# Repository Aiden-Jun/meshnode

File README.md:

# meshnode

A screenless Meshtastic node built around a Seeed Studio XIAO nRF52840 and a Wio-SX1262 LoRa module.

## Hardware

- **U1** — Seeed Studio XIAO nRF52840 (MCU + BLE, handles charging and USB)
- **U2** — Wio-SX1262 LoRa module
- **J1** — 2-pin JST 1.25mm connector for a single-cell LiPo battery
- **SW2** — slide switch, gates power to the LoRa radio only (see below)
- **J5 / J6** — solder pads for a hand-wired bodge to the XIAO's battery pads (see below)

## Repo contents

- `meshnode.kicad_pro` / `.kicad_sch` / `.kicad_pcb` — KiCad 8 project
- `meshnode.step` / `.wrl` — 3D board exports
- `Gerber/` — fabrication outputs (Gerbers + drill files)

## Building

Open `meshnode.kicad_pro` in KiCad. Run ERC and DRC before sending to fab

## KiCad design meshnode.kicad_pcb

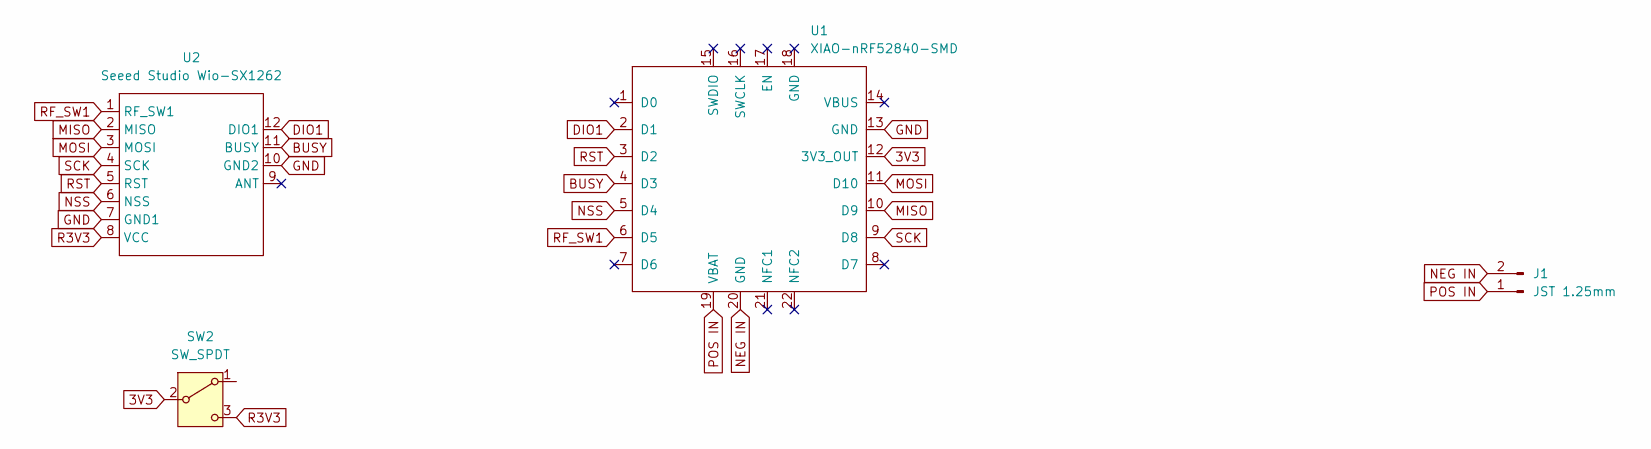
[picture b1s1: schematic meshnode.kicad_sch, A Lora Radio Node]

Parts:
J1: JST 1.25mm; Molex_PicoBlade_53048-0210_1x02_P1.25mm_Horizontal
SW2: SW_SPDT; SW_Slide_SPDT_Angled_CK_OS102011MA1Q
U1: XIAO-nRF52840-SMD
U2: Seeed Studio Wio-SX1262; Wio-SX1262 PCB Package

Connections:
3V3: SW2.2 (B), U1.12 (3V3_OUT)
BUSY: U1.4 (D3), U2.11 (BUSY)
DIO1: U1.2 (D1), U2.12 (DIO1)
GND: U1.13 (GND), U2.7 (GND1), U2.10 (GND2)
MISO: U1.10 (D9), U2.2 (MISO)
MOSI: U1.11 (D10), U2.3 (MOSI)
NEG IN: J1.2, U1.20 (GND)
NSS: U1.5 (D4), U2.6 (NSS)
POS IN: J1.1, U1.19 (VBAT)
R3V3: SW2.3 (C), U2.8 (VCC)
RF_SW1: U1.6 (D5), U2.1 (RF_SW1)
RST: U1.3 (D2), U2.5 (RST)
SCK: U1.9 (D8), U2.4 (SCK)

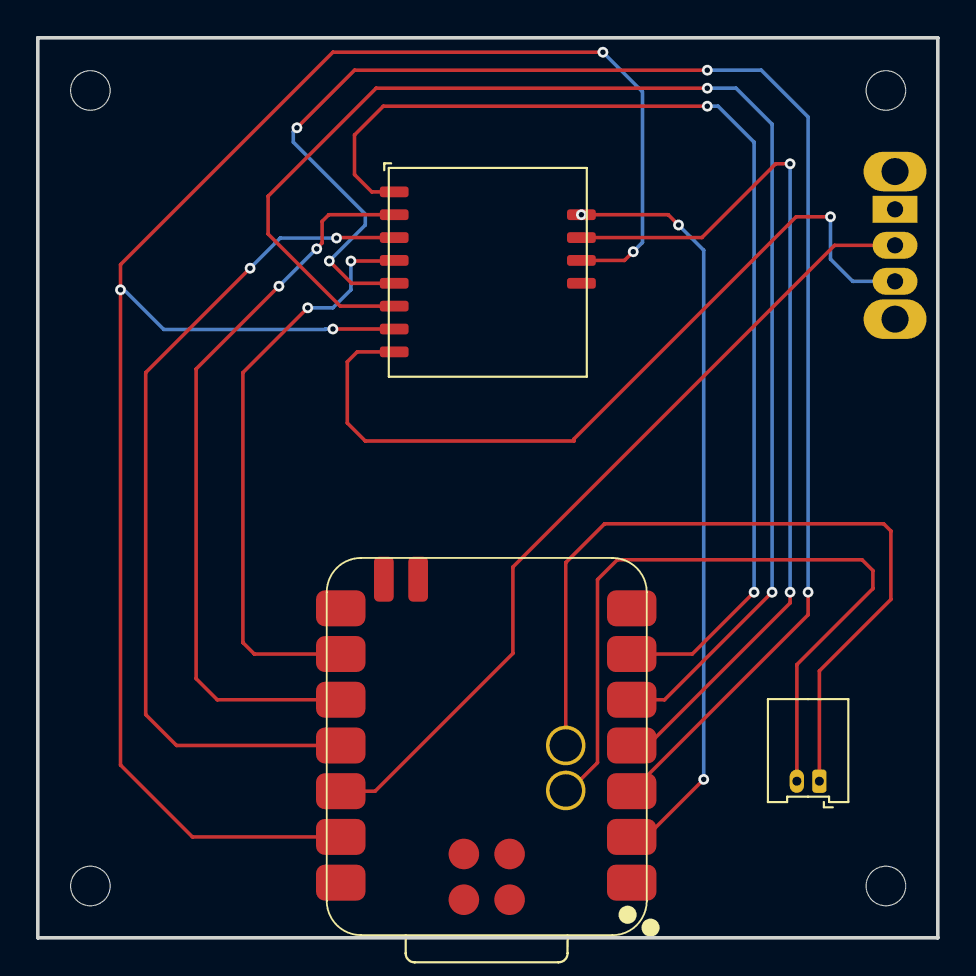
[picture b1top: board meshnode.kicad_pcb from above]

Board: 2 copper layers, 50.0 x 50.0 mm, 8 parts (1 on the bottom side), 13 nets.

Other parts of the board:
BL: MountingHole_2.2mm_M2
BR: MountingHole_2.2mm_M2
TL: MountingHole_2.2mm_M2
TR: MountingHole_2.2mm_M2
